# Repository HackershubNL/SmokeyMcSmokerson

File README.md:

# SmokeyMcSmokerson

## Introduction

This was inspired by the following projects:  
https://github.com/willblev/SmokeyTheBarrel  
https://github.com/jerrychangusa/ES96-Smart-Smoker  

Other sites and pages that were used in the process of making this project:  
https://amazingribs.com/  
https://genuineideas.com/ArticlesIndex/thecrutch.html

## Getting Started

The controller can be used separate from this smoker, meaning that you can use it on your own project. You will only need to place 4 of the 5 thermocouples in your smoker around the grill and have the fan blow into the bottom.

### Building the thing

It is currently in the last stages of design, as soon as the building starts, the build log will be published on: https://hackaday.io/project/165762-smokey-mc-smokerson  

### Running the thing

See Software/Controller for more info.

## Structure

```
-- Hardware  
  |-- Electronics - Design for the controller hardware  
  |-- Smoker - Design for the smoker itself  

-- Software  
  |-- Controller - Controller software

-- Images - Bunch of images
```

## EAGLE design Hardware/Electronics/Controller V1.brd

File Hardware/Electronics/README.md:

# Smokey Mc Smokerson - Controller Hardware

## Intro

This is revision number one, already some improvement points have been identified such as using standard fan connectors instead of screw terminals and additional smoothing capacitors need to be included.  
1/6/2019 - Latest .sch and .brd files have 4 pin fan headers instead of the screw terminals.

## Design Decisions

The SN74AHCT125N Buffer is added to level shift the PWM signal from 3.3v to 5v. This has been done for better compatibility with different fans. Certain ones seem to accept 3.3v PWM signal but most 12V fans seem to require a 5v signal.

Plans for the controller housing can be found in Hardware/Smoker.

Additional GPIO pins are available through the 6 pin header for future usage.

The fan which will be used is the Sanyo Denki 9GA0412P6G001*, this is chosen due to the high static pressure because it will need to blow through a hose and the airflow spreader.  
*https://nl.farnell.com/sanyo-denki/9ga0412p6g001/axial-fan-40mm-12vdc-14-8cfm-47dba/dp/2768815 

## Bill of Materials  

Farnell shopping cart csv is included but the following items are not on the list:  
- Raspberry Pi + SD card (Assuming you have one)
- Thermocouple boards and probes, see link to Aliexpress below
- Fans

And some items have a minimum order quantity so you will get more than required.

### Main board

- 5x 5-pin female headers
- 2x 3-pin screw terminals - In latest .sch and .brd files these are switched for 4 pin headers so you can use a PC fan without having to cut the wire. The fan I chose comes with leaded connectors.
- 1x 6-pin male header
- 1x 4-pin male header
- 1x 2-pin male header
- 1x 2-pin Molex Mini Fit Jr Header
- 1x 5.5mm Barrel Jack 
- 1x 14-pin DIP socket
- 1x 40-pin female GPIO header  
- 1x RECOM R-78B5.0-2.0 5V 2A DC/DC Converter - You can use alternatives to this such as the V7805-2000 or any other TO220 Switching Regulators. Opted for the 2A version due to minimal price difference and it's nice to have an overhead.
- 1x 10uF capacitor  
- 1x 22uF capacitor  
- 1x 220 ohm resistor  
- 1x SN74AHCT125N

### Raspberry Pi

- 1x Raspberry Pi Zero W  
- 1x 40-pin male GPIO header

### Control Panel

- 1x Adafruit LCD display with I2C board
- 1x Panel mount led indicator
- 1x Rocker Switch 
- 1x 2 pin Molex Mini Fit Jr Receptacle  
- 2x Molex Crimp Contacts  
- 2x female jumper wire soldered to led indicator  
- 4x female - female jumper wires for display to main board
- 8x 11mm M2.5 standoffs
- 8x M2.5 - 6mm screws
- 8x M2.5 nuts

### Sensors

- 5x MAX6675 Thermocouple boards with probe - https://nl.aliexpress.com/item/MAX6675-Module-K-Type-Thermocouple-Thermocouple-Senso-Temperature-Degrees-Module-for-arduino/32841448771.html

### Other

- 1 or 2 12V PWM fans (according to barbecue forums a single 10CFM fan should be sufficient)

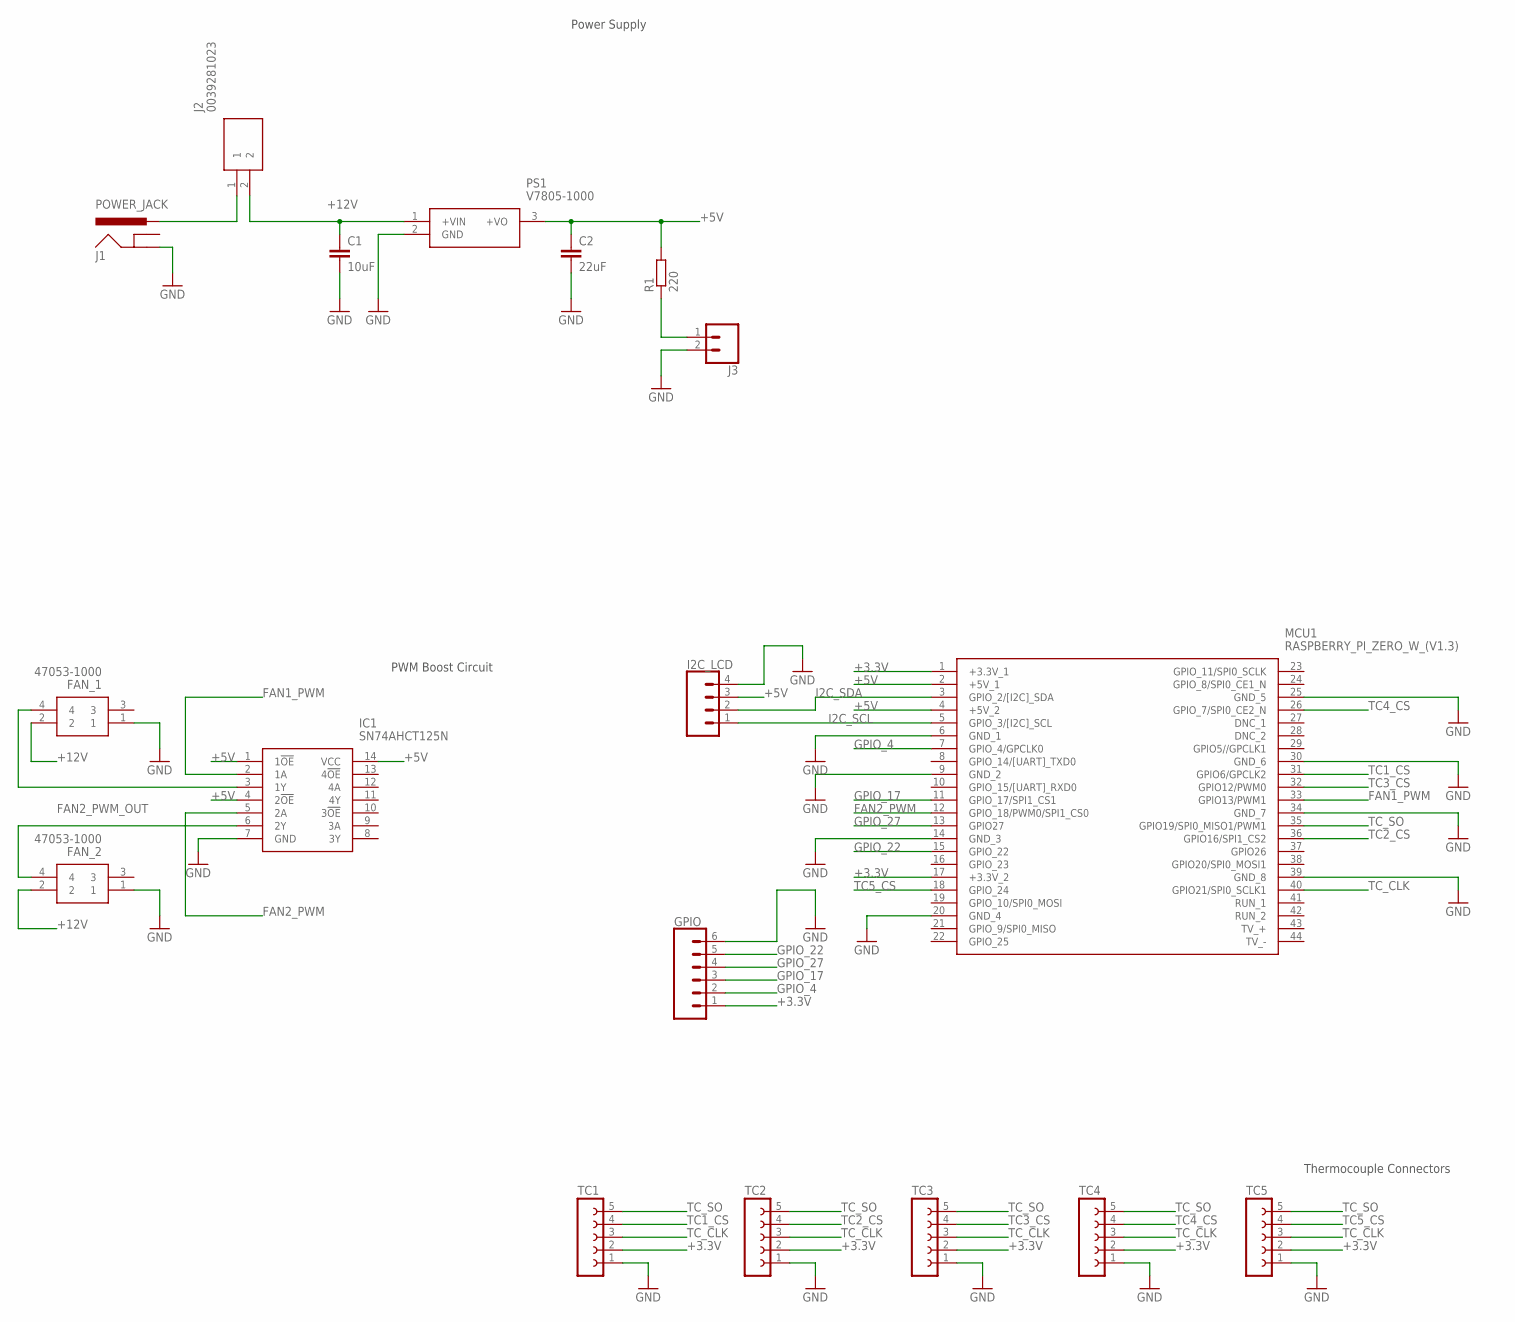
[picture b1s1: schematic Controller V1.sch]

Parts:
C1: 10uF; C050-024X044
C2: 22uF; C050-024X044
FAN_1, FAN_2: 47053-1000
GPIO: CONN_06SILK_FEMALE_PTH; 1X06
I2C_LCD: CONN_04PTH; 1X04
IC1: SN74AHCT125N; DIP794W53P254L1930H508Q14N
J1: POWER_JACK; POWER_JACK_PTH
J2: 0039281023; SHDR2W145P0X550_1X2_960X540X13
J3: CONN_02; 1X02
MCU1: RASPBERRY_PI_ZERO_W_(V1.3); RASPBERRYPIZEROWV13
PS1: V7805-1000; V78031500
R1: 220; 0309/10
TC1, TC2, TC3, TC4, TC5: FE05-1

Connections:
+3.3V: GPIO.1, MCU1.1 (+3.3V_1), MCU1.17 (+3.3V_2), TC1.2, TC2.2, TC3.2, TC4.2, TC5.2
+5V: C2.1, I2C_LCD.3, IC1.1 (1!OE), IC1.4 (2!OE), IC1.14 (VCC), MCU1.2 (+5V_1), MCU1.4 (+5V_2), PS1.3 (+VO), R1.2
+12V: C1.1, FAN_1.2, FAN_2.2, J2.2, PS1.1 (+VIN)
FAN1_PWM: IC1.2 (1A), MCU1.33 (GPIO13/PWM1)
FAN2_PWM: IC1.5 (2A), MCU1.12 (GPIO_18/PWM0/SPI1_CS0)
FAN2_PWM_OUT: FAN_2.4, IC1.6 (2Y)
FAN!_PWM_OUT: FAN_1.4, IC1.3 (1Y)
GND: C1.2, C2.2, FAN_1.1, FAN_2.1, GPIO.6, I2C_LCD.4, IC1.7 (GND), J1.GND, J3.2, MCU1.6 (GND_1), MCU1.9 (GND_2), MCU1.14 (GND_3), MCU1.20 (GND_4), MCU1.25 (GND_5), MCU1.30 (GND_6), MCU1.34 (GND_7), MCU1.39 (GND_8), PS1.2 (GND), TC1.1, TC2.1, TC3.1, TC4.1, TC5.1
GPIO_4: GPIO.2, MCU1.7 (GPIO_4/GPCLK0)
GPIO_17: GPIO.3, MCU1.11 (GPIO_17/SPI1_CS1)
GPIO_22: GPIO.5, MCU1.15 (GPIO_22)
GPIO_27: GPIO.4, MCU1.13 (GPIO27)
I2C_SCL: I2C_LCD.1, MCU1.5 (GPIO_3/[I2C]_SCL)
I2C_SDA: I2C_LCD.2, MCU1.3 (GPIO_2/[I2C]_SDA)
unnamed: J3.1, R1.1
TC1_CS: MCU1.31 (GPIO6/GPCLK2), TC1.4
TC2_CS: MCU1.36 (GPIO16/SPI1_CS2), TC2.4
TC3_CS: MCU1.32 (GPIO12/PWM0), TC3.4
TC4_CS: MCU1.26 (GPIO_7/SPI0_CE2_N), TC4.4
TC5_CS: MCU1.18 (GPIO_24), TC5.4
TC_CLK: MCU1.40 (GPIO21/SPI0_SCLK1), TC1.3, TC2.3, TC3.3, TC4.3, TC5.3
TC_SO: MCU1.35 (GPIO19/SPI0_MISO1/PWM1), TC1.5, TC2.5, TC3.5, TC4.5, TC5.5
VIN: J1.PWR, J2.1

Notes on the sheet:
Power Supply
PWM Boost Circuit
Thermocouple Connectors

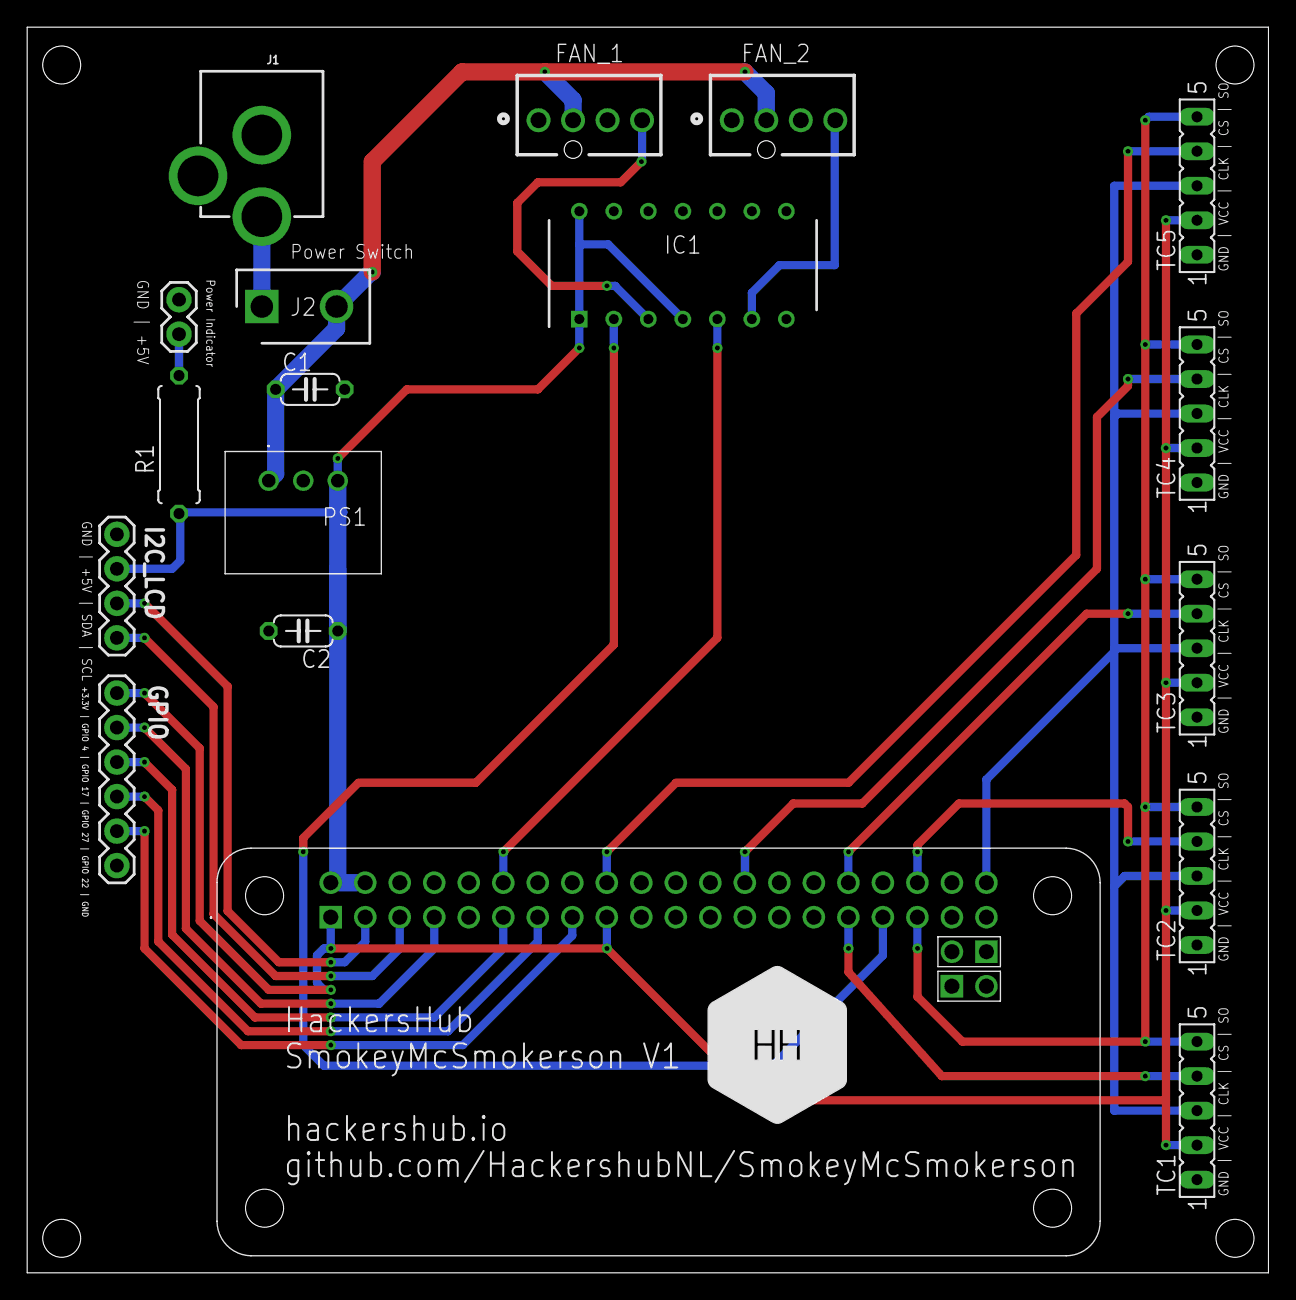
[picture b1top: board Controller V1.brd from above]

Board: 2 copper layers, 91.4 x 91.7 mm, 18 parts (0 on the bottom side), 23 nets.

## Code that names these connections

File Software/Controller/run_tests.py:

#!/usr/bin/python
# coding: utf8

import time

import Adafruit_GPIO.SPI as SPI
import MAX6675.MAX6675 as MAX6675

CLK_pin = 21
DO_pin = 19

TC1_CS_pin = 6
TC2_CS_pin = 16
TC3_CS_pin = 12
TC4_CS_pin = 7
TC5_CS_pin = 24

TC1 = MAX6675.MAX6675(CLK_pin, TC1_CS_pin, DO_pin)
TC2 = MAX6675.MAX6675(CLK_pin, TC2_CS_pin, DO_pin)
TC3 = MAX6675.MAX6675(CLK_pin, TC3_CS_pin, DO_pin)
TC4 = MAX6675.MAX6675(CLK_pin, TC4_CS_pin, DO_pin)
TC5 = MAX6675.MAX6675(CLK_pin, TC5_CS_pin, DO_pin)

TC1_temp = TC1.readTempC()
time.sleep(1000)
TC2_temp = TC2.readTempC()
time.sleep(1000)
TC3_temp = TC3.readTempC()
time.sleep(1000)
TC4_temp = TC4.readTempC()
time.sleep(1000)
TC5_temp = TC5.readTempC()

print("Thermocouple 1 temperature: " + TC1_temp + " Celcius")
print("Thermocouple 2 temperature: " + TC2_temp + " Celcius")
print("Thermocouple 3 temperature: " + TC3_temp + " Celcius")
print("Thermocouple 4 temperature: " + TC4_temp + " Celcius")
print("Thermocouple 5 temperature: " + TC5_temp + " Celcius")

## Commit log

2019-05-26 Create LICENSE
2019-05-28 Update to basic working version
2019-05-28 Revert "Update to basic working version"
    This reverts commit d02105a139e514b22ce7739d7c3cd99efc8185a7.
2019-05-28 Revert "Revert "Update to basic working version""
    This reverts commit 48b70cc33131ed02f2104fd57b75453119ada5e7.
2019-05-29 Bunch of changes for logging, easier reading etc
2019-05-30 Small updates
2019-05-30 Running Blynk server as service and update setup script
2019-05-31 Renamed recipes file, added Blynk QR code and Readme update, delete pycache
2019-06-01 Changed screw terminals for actual 4 pin PWM fan headers
2019-06-01 Readme and recipes update
2019-06-01 Update Blynk Server properties
2019-06-01 Small updates and bug fixes
2019-08-24 Whole bunch of changes coming from hardware testing
2019-09-12 Small clean up items and upgrade to latest blynk server version
2019-09-12 Update of system services both for the Blynk server and the Smokey service. Added temperature offset option to the config file and temperature controller.
2019-09-12 Updated Blynk App
2019-09-12 Minor recipe updates
2019-09-17 Minor update
2019-09-17 Added lid open functionality
2019-09-18 Added temperature calibration function
2019-09-20 Added graceful shutdown when killing the process
2019-09-20 Bug fixes
2019-09-20 Changes to temperature offset calibration
2019-09-20 Minor changes

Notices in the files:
parts and their libraries:
SparkFun-Connectors: Licensing: Creative Commons ShareAlike 4.0 International - https://creativecommons.org/licenses/by-sa/4.0
